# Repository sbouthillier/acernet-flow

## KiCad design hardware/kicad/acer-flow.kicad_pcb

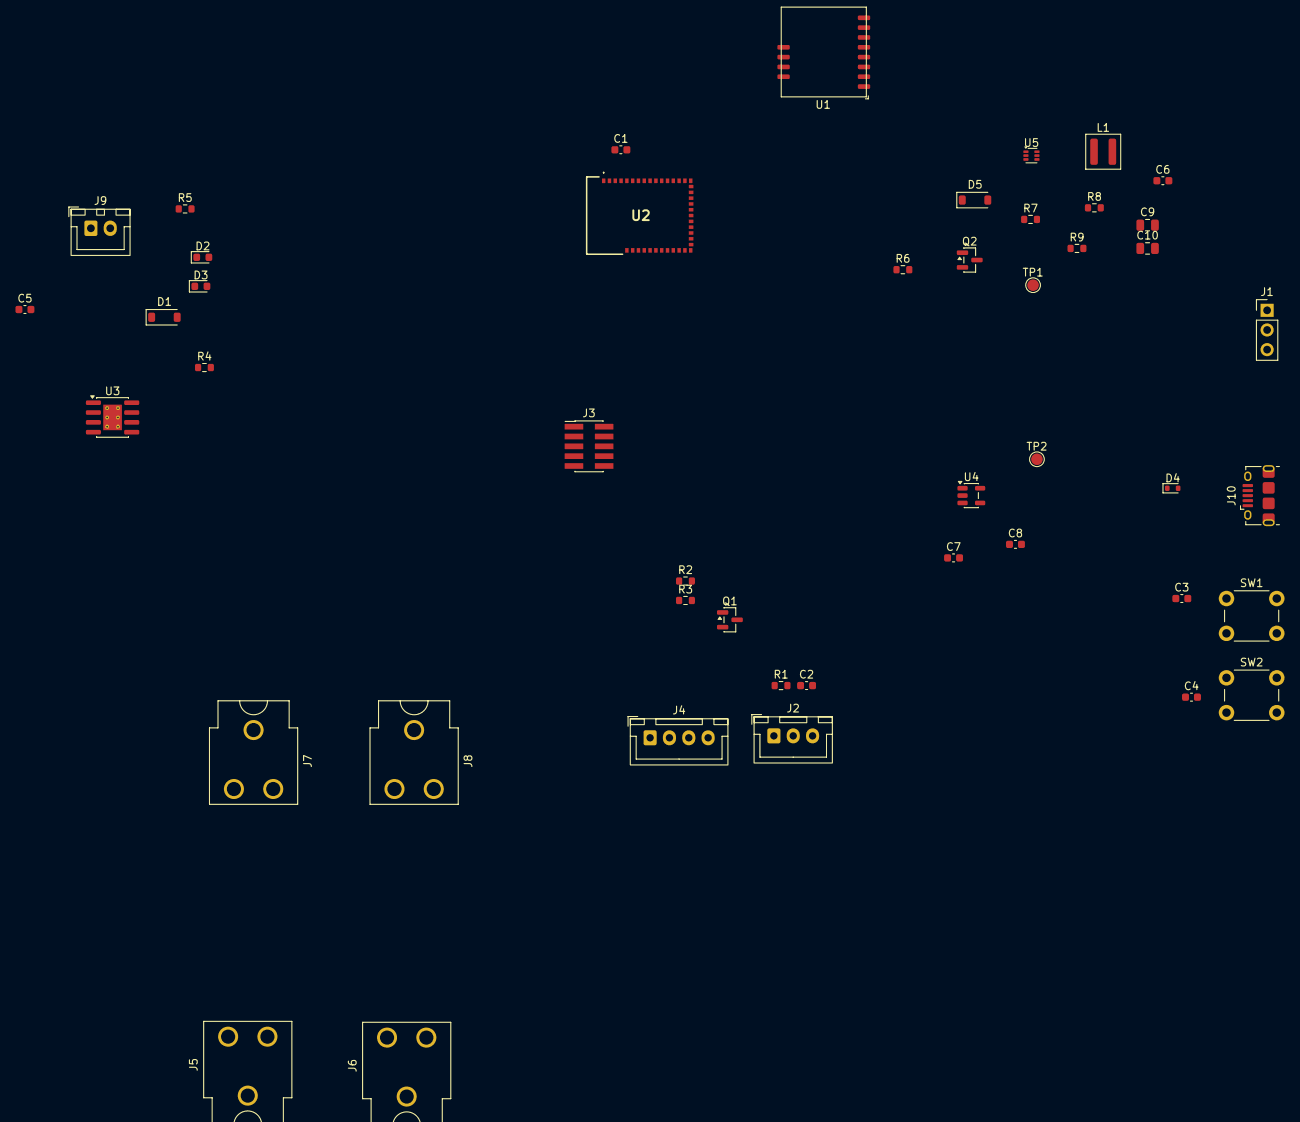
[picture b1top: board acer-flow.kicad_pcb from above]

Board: 2 copper layers, 46 parts (0 on the bottom side), 34 nets, no tracks yet.

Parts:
C1: 0.1uF; C_0603_1608Metric
C2: 100nF; C_0603_1608Metric
C3, C4: 1nF; C_0603_1608Metric
C5, C6, C7, C8: 10uF; C_0603_1608Metric
C9, C10: 22uF; C_0805_2012Metric
D1, D5: 1N5817; D_SOD-123
D2: Blue 2.9V; LED_0603_1608Metric
D3: Green 3.2V; LED_0603_1608Metric
D4: LESD5D5.0CT1G; D_SOD-523
J1: Conn_01x03; PinHeader_1x03_P2.54mm_Vertical
J2: Conn_01x03; JST_XH_B3B-XH-A_1x03_P2.50mm_Vertical
J3: JTAG / SWD; PinHeader_2x05_P1.27mm_Vertical_SMD
J4: Conn_01x04; JST_XH_B4B-XH-A_1x04_P2.50mm_Vertical
J5, J6, J7, J8: Conn_01x01_Socket; BatteryClip_Keystone_54_D16-19mm
J9: Solar; JST_XH_B2B-XH-A_1x02_P2.50mm_Vertical
J10: USB_B_Micro; USB_Micro-B_Amphenol_10118194-0001LF_Horizontal
L1: 1uH; L_Coilcraft_XAL4030-XXX
Q1, Q2: AO3401A; SOT-23
R1: 4K7; R_0603_1608Metric
R2: 100; R_0603_1608Metric
R3, R6, R7, R9: 100K; R_0603_1608Metric
R4: 180; R_0603_1608Metric
R5: 2k4; R_0603_1608Metric
R8: 732K; R_0603_1608Metric
SW1: RESET; SW_PUSH_6mm
SW2: USER; SW_PUSH_6mm
TP1: 5V; TestPoint_Pad_D1.5mm
TP2: 3.3V; TestPoint_Pad_D1.5mm
U1: WIO-SX1262; Wio-SX1262-SB
U2: 453-00001R; 45300001R
U3: CN3158; SOIC-8-1EP_3.9x4.9mm_P1.27mm_EP2.41x3.3mm_ThermalVias
U4: TLV75533PDBV; SOT-23-5
U5: TPS61023; SOT-563

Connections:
+3.3V: C1.1, C8.1, J3.1, Q1.2 (S), R3.1, TP2.1 (1_1), U1.8 (VCC), U2.26 (VDD_NRF), U4.5 (OUT)
+5V: C7.1, C9.1, C10.1, R8.1, TP1.1 (1_1), U4.1 (IN), U4.3 (EN), U5.6 (VOUT)
/Mcu/BUSY: U1.11 (BUSY), U2.24 (P1.01/XL2_)
/Mcu/DIO1: U1.12 (DIO1), U2.25 (P1.00/XL1_)
/Mcu/MISO: U1.2 (MISO), U2.11 (P2.04)
/Mcu/MOSI: U1.3 (MOSI), U2.8 (P2.02_)
/Mcu/NRESET: C3.1, J3.10, SW1.1, U2.7 (NRESET)
/Mcu/NSS: U1.6 (NSS), U2.12 (P2.05)
/Mcu/RF_SW: U1.1 (RF_SW1), U2.9 (P2.00)
/Mcu/RST: U1.5 (RST), U2.13 (P2.03)
/Mcu/RXD: J1.1, U2.4 (P2.07)
/Mcu/SCK: U1.4 (SCK), U2.10 (P2.01/CLK)
/Mcu/SNR_RX: J4.4, U2.19 (P0.02)
/Mcu/SNR_TX: J4.3, U2.18 (P0.01_)
/Mcu/SWDCLK: J3.4, U2.6 (SWDCLK)
/Mcu/SWDIO: J3.2, U2.5 (SWDIO)
/Mcu/TEMP_DATA: C2.1, J2.2, R1.2, U2.14 (P1.03/NFC2/CLK)
/Mcu/TXD: J1.2, U2.3 (P2.08)
/Mcu/USER: C4.1, SW2.1, U2.17 (P0.00_)
/Mcu/VEXT_EN: R2.1, U2.15 (P1.02/NFC1_)
GND: C1.2, C2.2, C3.2, C4.2, C5.2, C6.2, C7.2, C8.2, C9.2, C10.2, D4.2 (A2), J1.3, J2.3, J3.3, J3.5, J3.9, J4.2, J6.1 (Pin_1_1), J8.1 (Pin_1_1), J9.2, J10.5 (GND), J10.SH (Shield), R5.2, R6.2, R9.2, SW1.2, SW2.2, U1.7 (GND1), U1.10 (GND2), U2.1 (GND_1), U2.16 (GND_2), U2.27 (GND_3), U2.39 (GND_4), U3.1 (TEMP), U3.3 (GND), U3.9 (GND), U4.2 (GND), U5.4 (GND)
unnamed: D1.2 (A), J9.1
unnamed: D2.2 (A), D3.2 (A), R4.2
unnamed: D2.1 (K), U3.7 (~CHRG)
unnamed: D3.1 (K), U3.6 (~DONE)
unnamed: C6.1, D5.1 (K), L1.1, Q2.2 (S), R7.1, U5.3 (VIN)
unnamed: Q1.1 (G), R2.2, R3.2
unnamed: R5.1, U3.2 (ISET)
unnamed: R7.2, U5.2 (EN)
unnamed: R8.2, R9.1, U5.1 (FB)
unnamed: L1.2, U5.5 (SW)
Vbatt: C5.1, J5.1 (Pin_1_1), J7.1 (Pin_1_1), Q2.3 (D), U3.5 (BAT), U3.8 (FB)
Vbus: D1.1 (K), D4.1 (A1), D5.2 (A), J10.1 (VBUS), Q2.1 (G), R4.1, R6.1, U3.4 (VIN)
Vext: J2.1, J4.1, Q1.3 (D), R1.1

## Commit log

2026-06-23 Adding KiCad files
2026-06-25 Replacing MCU ESP32 by nRF54L15
2026-06-30 Adding footprints. Starting layout
